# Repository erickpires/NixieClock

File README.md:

# The Project

This is a clock that uses Nixie Tubes as display. The idea is not new and there are hundreds of others Nixie based clock on the internet.
I got inspired to build the clock after watching a video from [Techmoan](https://www.youtube.com/channel/UC5I2hjZYiW9gZPVkvzM8_Cw).

## The Nixies

The Nixie Tubes were bought from eBay. They are IN-14 tubes desoldered from unused replacement board for old equipment (so the seller told me).

To drive the Nixies, six K155ID1 (the Russian version of the 74141) were also bought from eBay (which turned out to be a bad idea since those chips are very old, not reliable and consume too much power).

The Nixies are powered with 170V and half of their nominal amperage (this should extend their lifetime).

## The Boards

The clock is divided in three boards: a High-Voltage Power Supply for the Nixie Tubes, a Logic Board and a board to hold the Nixies.

* The Power Supply was built on a prototyping PCB based on two designs found online. More information can be found on the Power Supply directory of this repository.

* The Logic Board contains an Atmel Atmega 328p microcontroller which implements the clock in software. This board also contains some passive components and connectors. The schematic and the PCB design was done using kicad and can be found under the kicad/LowerBoard directory. The board itself was homemade using the toner transfer technique (more information can be found online) and etched using ferric chloride.

* The third board holds the Nixie Tubes as well as the six driver ICs and three 74HC573 8-bit transparent latches. This board also functions as the upper face of the clock and the ICs were put in this board because I thought it would be more aesthetically pleasing. The PCB design can be found under the kicad/Clock directory. This board was made using the same technique as the Logic Board.

## The Code

The code runs on an Atmega 328p with an Arduino bootloader. The code doesn't use any of the Arduino library functions, accessing registers directly. The code should work fine without the Arduino environment and using the Atmel Studio. The Arduino environment is used only to provide a n easy way of uploading the code into the microcontroller.

The clock is implemented in software, as already mentioned. The code also handles debouncing of the input buttons and rotary encoder.

Every whole minute the clock plays an animation in which all digits of all Nixie Tubes are lit twice. The primary reason for the animation is to avoid [Cathode Poisoning](http://www.tube-tester.com/sites/nixie/different/cathode%20poisoning/cathode-poisoning.htm) since must of the digits don't change too often (and some digits aren't even lit) but also because it looks cool.

From midnight to 6AM the display is shutdown. This should save some lifetime out of the Nixies. Upon interaction with any button (or rotary encoder) while the display is off, it turns on for 5 seconds.

An alarm clock functionality is planned, but not yet implemented.

## Final Result

Here are two photos of the clock working.

and a video:

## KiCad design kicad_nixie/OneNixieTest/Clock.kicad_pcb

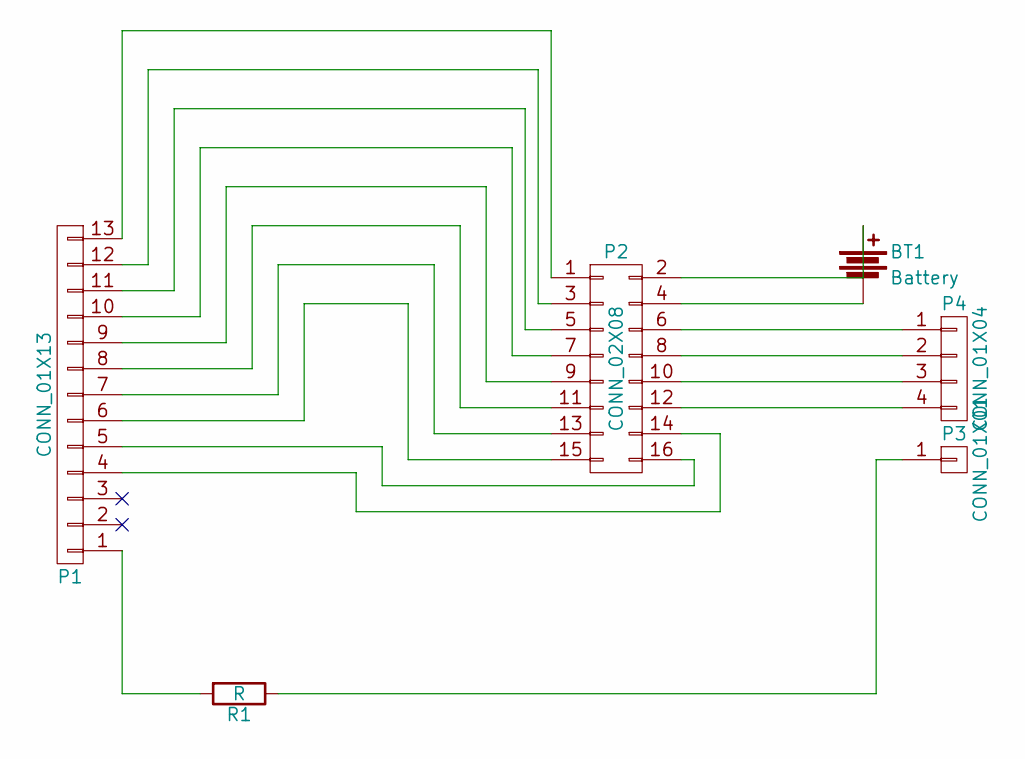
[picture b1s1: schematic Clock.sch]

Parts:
BT1: Battery; Pin_Header_Straight_1x02
P1: CONN_01X13; IN-14-mod
P2: CONN_02X08; DIP-16_W7.62mm_LongPads
P3: CONN_01X01; Pin_Header_Straight_1x01
P4: CONN_01X04; Pin_Header_Straight_1x04
R1: R; Resistor_Horizontal_RM10mm

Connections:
unnamed: BT1.1, P2.2
unnamed: BT1.2, P2.4
unnamed: P1.1, R1.2
unnamed: P1.4, P2.14
unnamed: P1.5, P2.16
unnamed: P1.6, P2.15
unnamed: P1.7, P2.13
unnamed: P1.8, P2.11
unnamed: P1.9, P2.9
unnamed: P1.10, P2.7
unnamed: P1.11, P2.5
unnamed: P1.12, P2.3
unnamed: P1.13, P2.1
unnamed: P2.6, P4.1
unnamed: P2.8, P4.2
unnamed: P2.10, P4.3
unnamed: P2.12, P4.4
unnamed: P3.1, R1.1

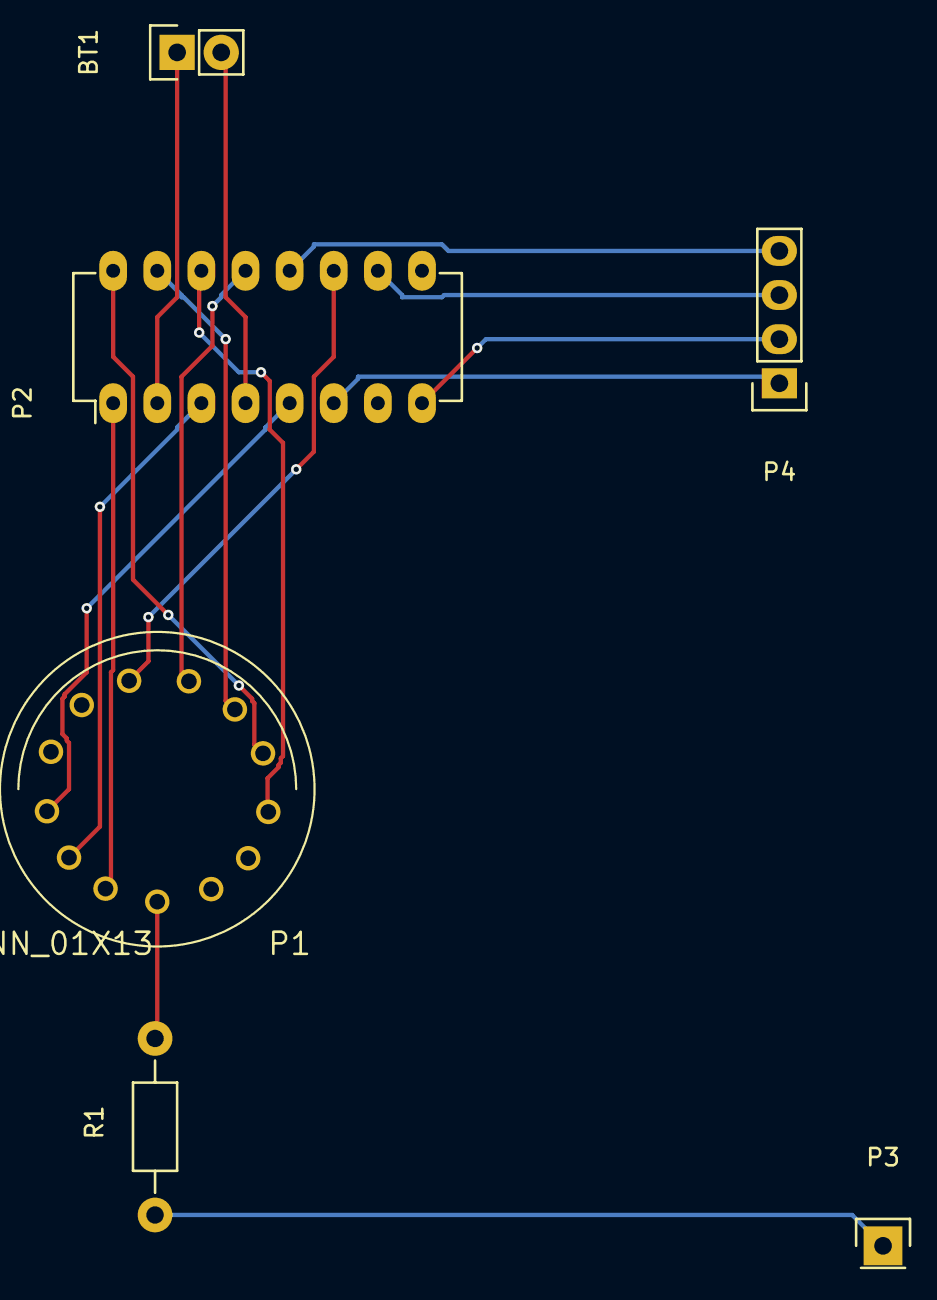
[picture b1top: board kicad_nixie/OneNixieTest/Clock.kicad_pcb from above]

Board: 2 copper layers, 6 parts (0 on the bottom side), 18 nets.

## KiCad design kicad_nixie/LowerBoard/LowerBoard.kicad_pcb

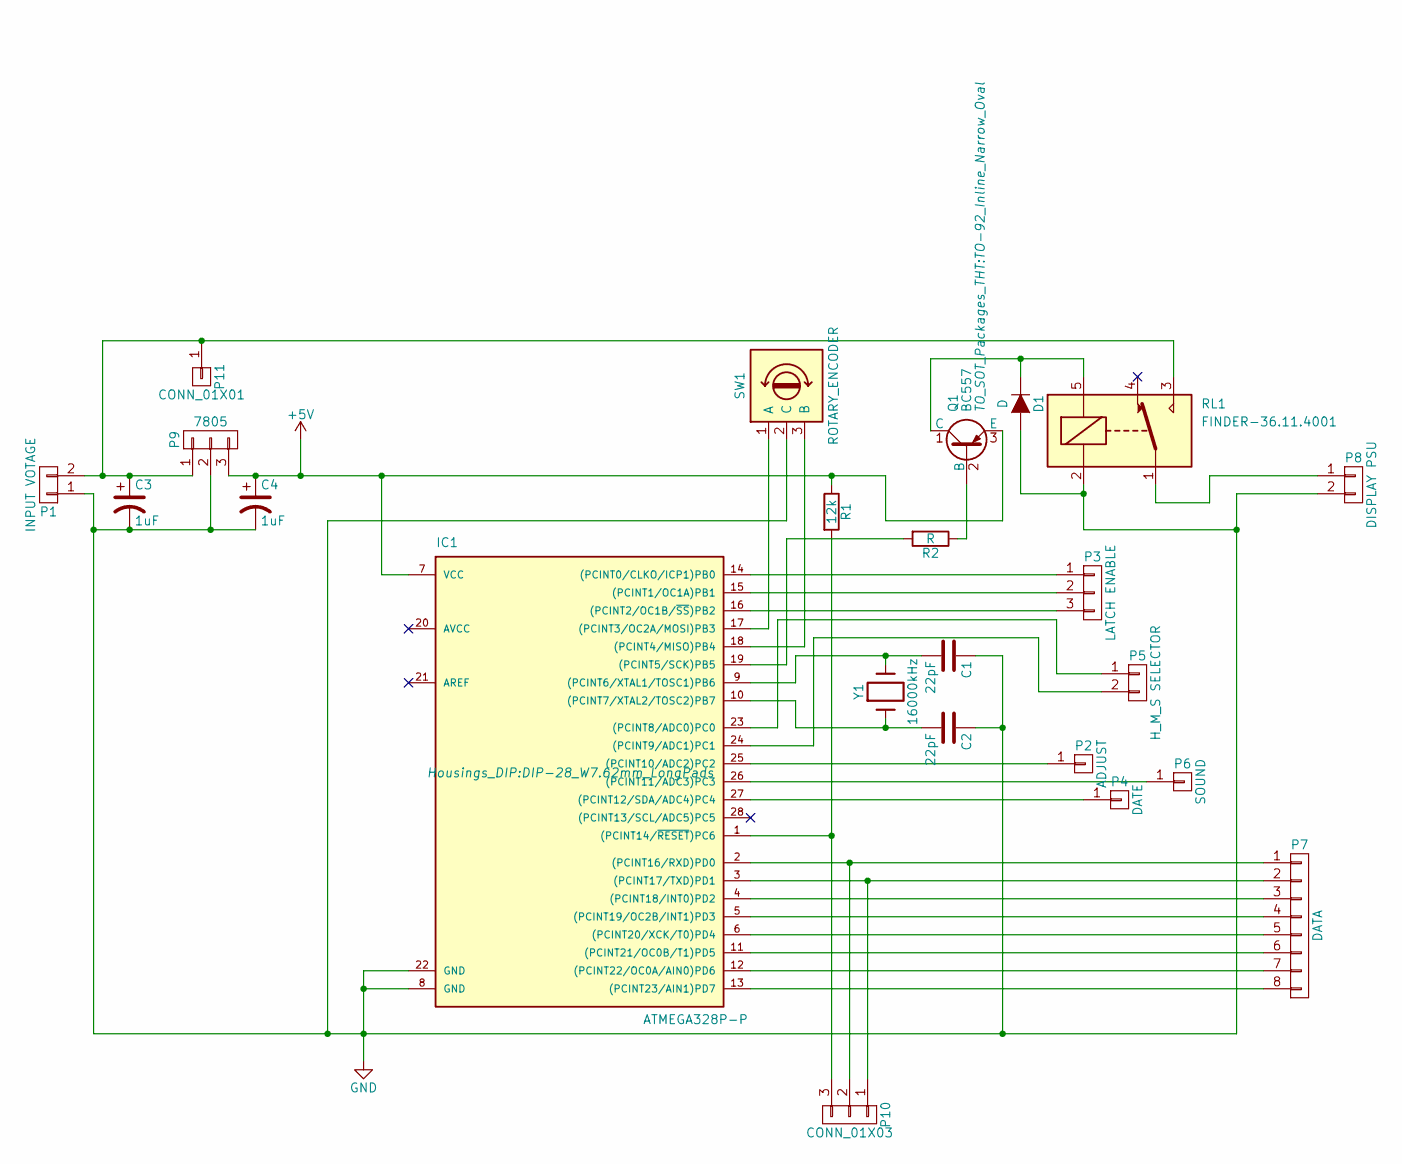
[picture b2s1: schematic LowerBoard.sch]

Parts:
C1, C2: 22pF; C_Disc_D3_P2.5
C3, C4: 1uF; C_Radial_D5_L11_P2.5
D1: D; Diode_DO-35_SOD27_Horizontal_RM10
IC1: ATMEGA328P-P; DIP-28_W7.62mm_LongPads
P1: INPUT VOTAGE; Pin_Header_Straight_1x02
P2: ADJUST; Pin_Header_Straight_1x01
P3: LATCH ENABLE; Pin_Header_Straight_1x03
P4: DATE; Pin_Header_Straight_1x01
P5: H_M_S SELECTOR; Pin_Header_Straight_1x02
P6: SOUND; Pin_Header_Straight_1x01
P7: DATA; Pin_Header_Straight_1x08
P8: DISPLAY PSU; Pin_Header_Straight_1x02
P9: 7805; TO-220
P10: CONN_01X03; Pin_Header_Straight_1x03
P11: CONN_01X01; Pin_Header_Straight_1x01
Q1: BC557; TO-92_Inline_Narrow_Oval
R1: 12k; Resistor_Horizontal_RM7mm
R2: R; Resistor_Horizontal_RM7mm
RL1: FINDER-36.11.4001; Relay_SANYOU_SRD_Series_Form_C
SW1: ROTARY_ENCODER; Pin_Header_Straight_1x03
Y1: 16000kHz; Crystal_HC50-U_Vertical

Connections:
+5V: C4.1, IC1.7 (VCC), P9.3, Q1.3 (E), R1.1
GND: C1.1, C2.1, C3.2, C4.2, D1.2 (A), IC1.8 (GND), IC1.22 (GND), P1.1, P8.2, P9.2, RL1.2, SW1.2 (C)
unnamed: C1.2, IC1.9 ((PCINT6/XTAL1/TOSC1)PB6), Y1.2
unnamed: C2.2, IC1.10 ((PCINT7/XTAL2/TOSC2)PB7), Y1.1
unnamed: C3.1, P1.2, P9.1, P11.1, RL1.3
unnamed: D1.1 (K), Q1.1 (C), RL1.5
unnamed: IC1.1 ((PCINT14/~RESET~)PC6), P10.3, R1.2
unnamed: IC1.2 ((PCINT16/RXD)PD0), P7.1, P10.2
unnamed: IC1.3 ((PCINT17/TXD)PD1), P7.2, P10.1
unnamed: IC1.4 ((PCINT18/INT0)PD2), P7.3
unnamed: IC1.5 ((PCINT19/OC2B/INT1)PD3), P7.4
unnamed: IC1.6 ((PCINT20/XCK/T0)PD4), P7.5
unnamed: IC1.11 ((PCINT21/OC0B/T1)PD5), P7.6
unnamed: IC1.12 ((PCINT22/OC0A/AIN0)PD6), P7.7
unnamed: IC1.13 ((PCINT23/AIN1)PD7), P7.8
unnamed: IC1.14 ((PCINT0/CLKO/ICP1)PB0), P3.1
unnamed: IC1.15 ((PCINT1/OC1A)PB1), P3.2
unnamed: IC1.16 ((PCINT2/OC1B/~SS~)PB2), P3.3
unnamed: IC1.17 ((PCINT3/OC2A/MOSI)PB3), SW1.1 (A)
unnamed: IC1.18 ((PCINT4/MISO)PB4), SW1.3 (B)
unnamed: IC1.19 ((PCINT5/SCK)PB5), R2.2
unnamed: IC1.23 ((PCINT8/ADC0)PC0), P5.1
unnamed: IC1.24 ((PCINT9/ADC1)PC1), P5.2
unnamed: IC1.25 ((PCINT10/ADC2)PC2), P2.1
unnamed: IC1.26 ((PCINT11/ADC3)PC3), P6.1
unnamed: IC1.27 ((PCINT12/SDA/ADC4)PC4), P4.1
unnamed: P8.1, RL1.1
unnamed: Q1.2 (B), R2.1

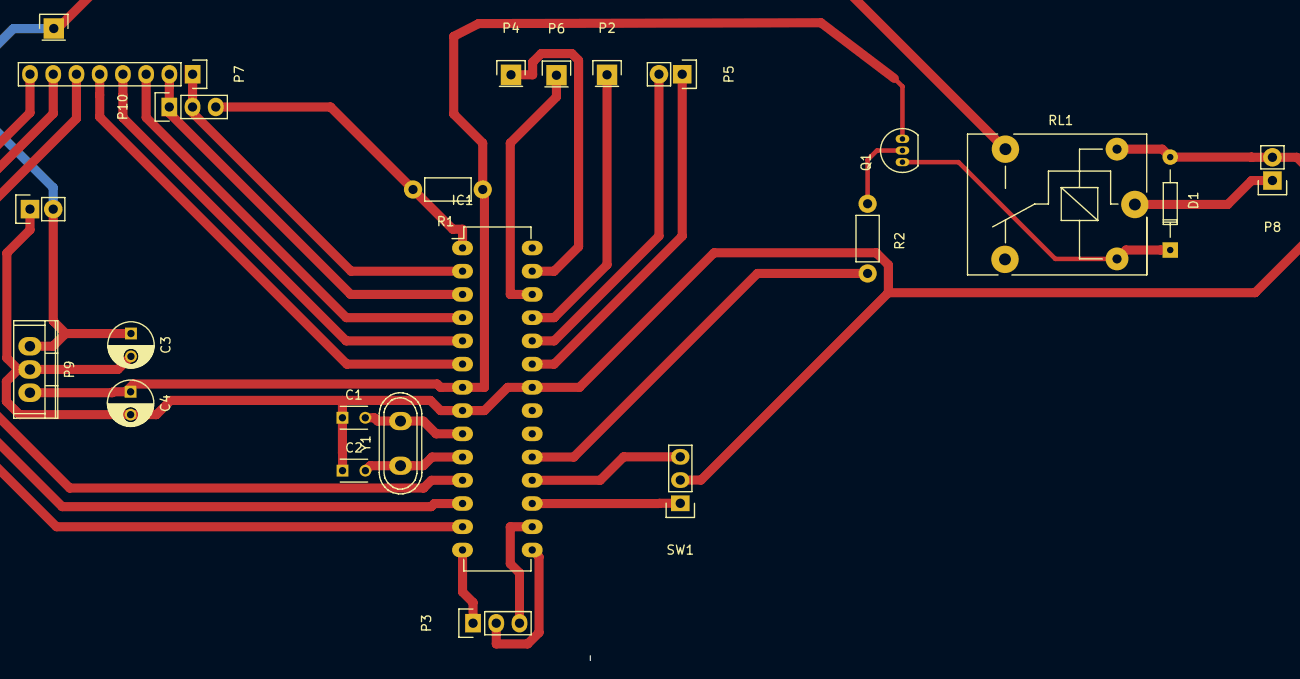
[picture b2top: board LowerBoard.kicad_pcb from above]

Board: 2 copper layers, 23 parts (0 on the bottom side), 28 nets.

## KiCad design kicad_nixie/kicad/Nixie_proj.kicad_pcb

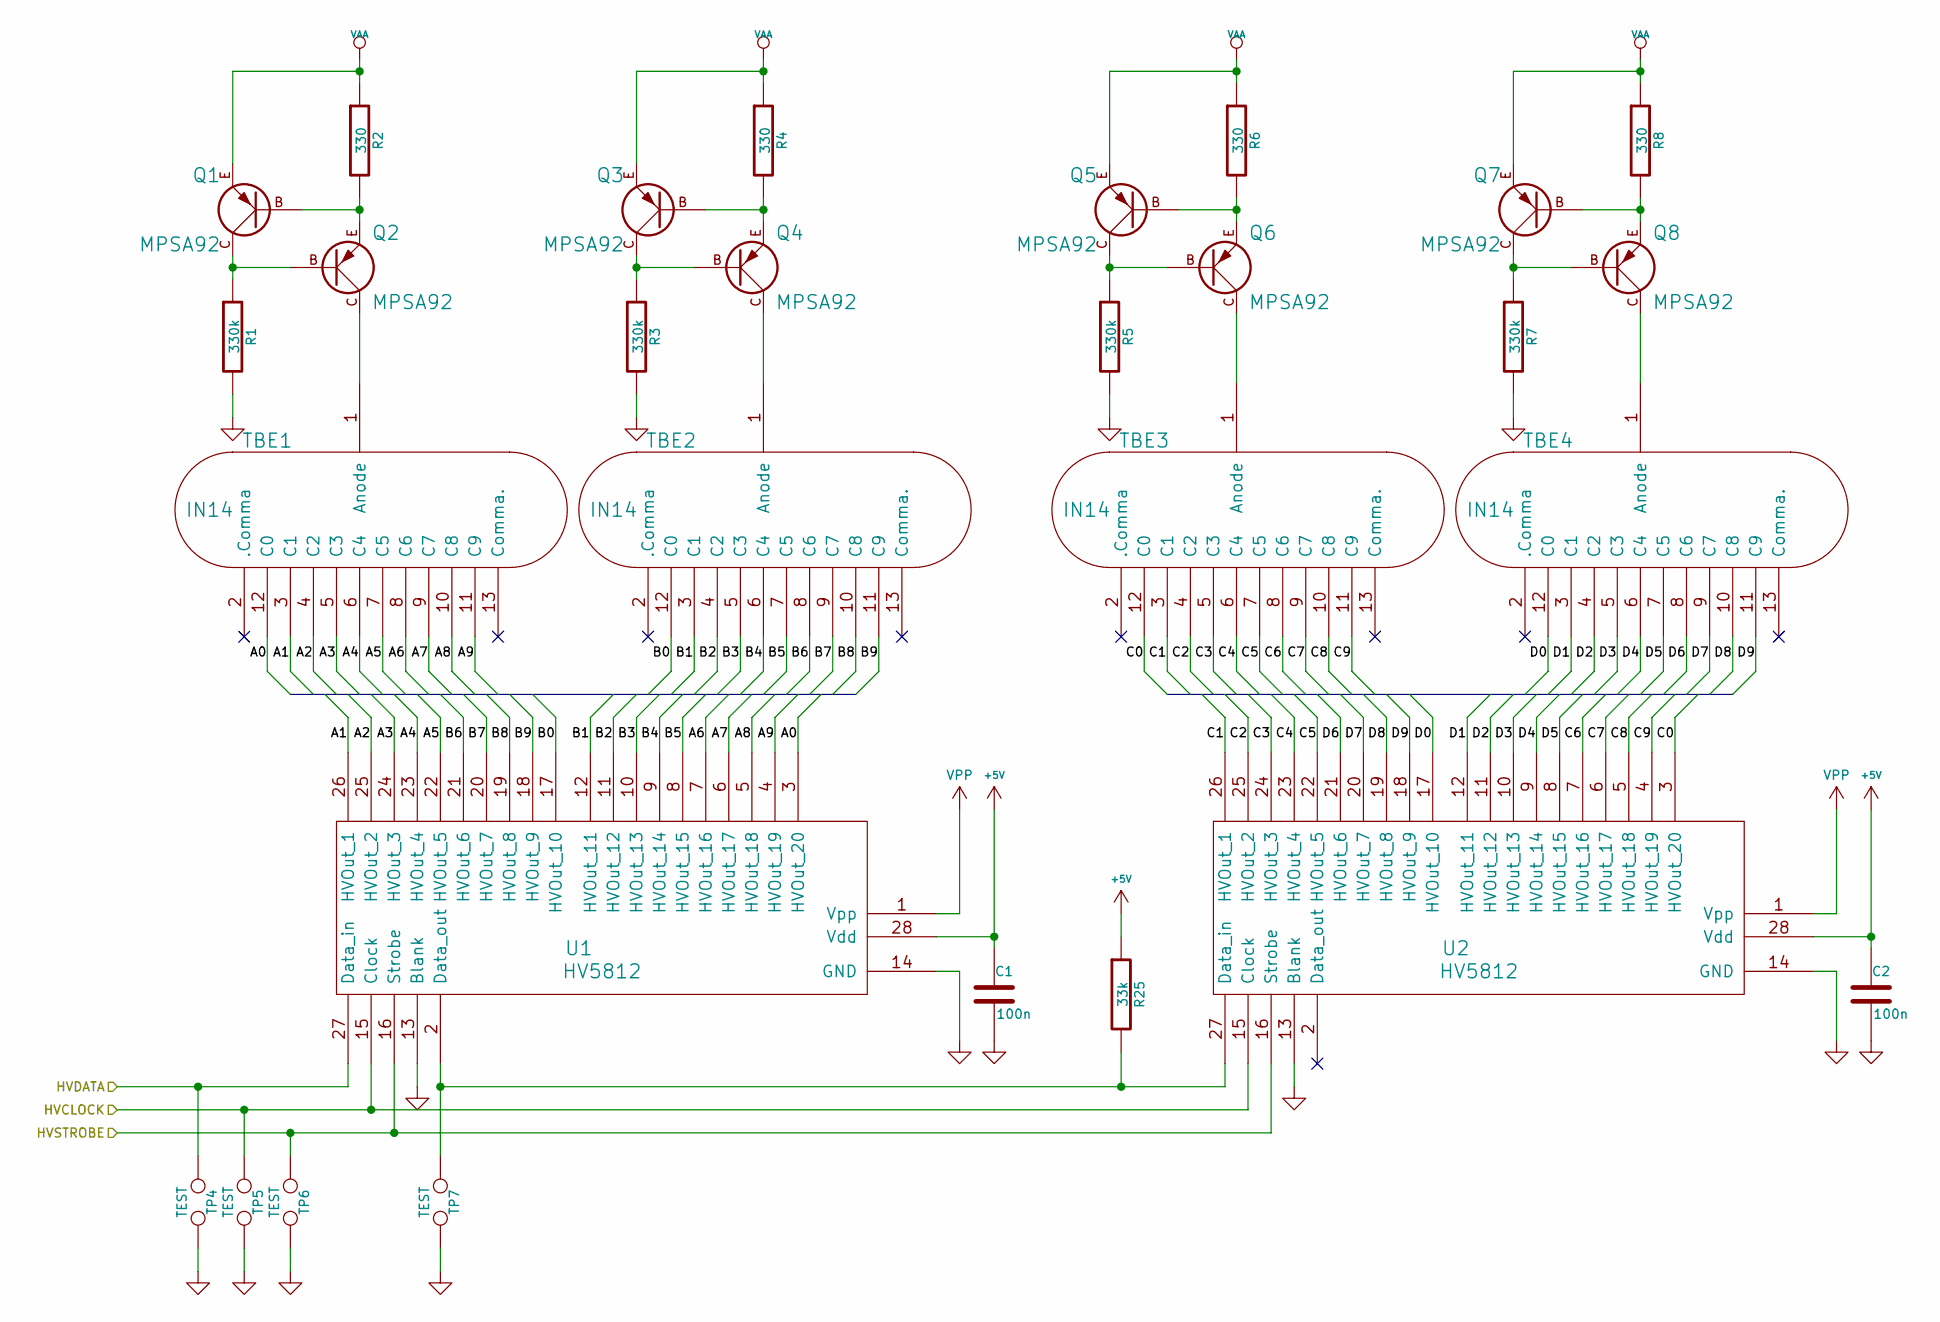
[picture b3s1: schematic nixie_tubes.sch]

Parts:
C1, C2: 100n; c_0805
Q1, Q2, Q3, Q4, Q5, Q6, Q7, Q8: MPSA92; TO92-CBE
R1, R3, R5, R7: 330k; R3-mod
R2, R4, R6, R8: 330; R3-mod
R25: 33k; R0805_smd-mod
TBE1, TBE2, TBE3, TBE4: IN14; IN-14-mod
TP4, TP5, TP6, TP7: TEST; GS2
U1, U2: HV5812; SO28W-mod

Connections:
+5V: C1.1, C2.1, R25.1, U1.28 (Vdd), U2.28 (Vdd); also elsewhere on the board
/Microcontroller and clock/HVCLOCK: TP5.1, U1.15 (Clock), U2.15 (Clock); also elsewhere on the board
/Microcontroller and clock/HVDATA: TP4.1, U1.27 (Data_in); also elsewhere on the board
/Microcontroller and clock/HVSTROBE: TP6.1, U1.16 (Strobe), U2.16 (Strobe); also elsewhere on the board
/Tubes with drivers/A0: TBE1.12 (C0), U1.3 (HVOut_20)
/Tubes with drivers/A1: TBE1.3 (C1), U1.26 (HVOut_1)
/Tubes with drivers/A2: TBE1.4 (C2), U1.25 (HVOut_2)
/Tubes with drivers/A3: TBE1.5 (C3), U1.24 (HVOut_3)
/Tubes with drivers/A4: TBE1.6 (C4), U1.23 (HVOut_4)
/Tubes with drivers/A5: TBE1.7 (C5), U1.22 (HVOut_5)
/Tubes with drivers/A6: TBE1.8 (C6), U1.7 (HVOut_16)
/Tubes with drivers/A7: TBE1.9 (C7), U1.6 (HVOut_17)
/Tubes with drivers/A8: TBE1.10 (C8), U1.5 (HVOut_18)
/Tubes with drivers/A9: TBE1.11 (C9), U1.4 (HVOut_19)
/Tubes with drivers/B0: TBE2.12 (C0), U1.17 (HVOut_10)
/Tubes with drivers/B1: TBE2.3 (C1), U1.12 (HVOut_11)
/Tubes with drivers/B2: TBE2.4 (C2), U1.11 (HVOut_12)
/Tubes with drivers/B3: TBE2.5 (C3), U1.10 (HVOut_13)
/Tubes with drivers/B4: TBE2.6 (C4), U1.9 (HVOut_14)
/Tubes with drivers/B5: TBE2.7 (C5), U1.8 (HVOut_15)
/Tubes with drivers/B6: TBE2.8 (C6), U1.21 (HVOut_6)
/Tubes with drivers/B7: TBE2.9 (C7), U1.20 (HVOut_7)
/Tubes with drivers/B8: TBE2.10 (C8), U1.19 (HVOut_8)
/Tubes with drivers/B9: TBE2.11 (C9), U1.18 (HVOut_9)
/Tubes with drivers/C0: TBE3.12 (C0), U2.3 (HVOut_20)
/Tubes with drivers/C1: TBE3.3 (C1), U2.26 (HVOut_1)
/Tubes with drivers/C2: TBE3.4 (C2), U2.25 (HVOut_2)
/Tubes with drivers/C3: TBE3.5 (C3), U2.24 (HVOut_3)
/Tubes with drivers/C4: TBE3.6 (C4), U2.23 (HVOut_4)
/Tubes with drivers/C5: TBE3.7 (C5), U2.22 (HVOut_5)
/Tubes with drivers/C6: TBE3.8 (C6), U2.7 (HVOut_16)
/Tubes with drivers/C7: TBE3.9 (C7), U2.6 (HVOut_17)
/Tubes with drivers/C8: TBE3.10 (C8), U2.5 (HVOut_18)
/Tubes with drivers/C9: TBE3.11 (C9), U2.4 (HVOut_19)
/Tubes with drivers/D0: TBE4.12 (C0), U2.17 (HVOut_10)
/Tubes with drivers/D1: TBE4.3 (C1), U2.12 (HVOut_11)
/Tubes with drivers/D2: TBE4.4 (C2), U2.11 (HVOut_12)
/Tubes with drivers/D3: TBE4.5 (C3), U2.10 (HVOut_13)
/Tubes with drivers/D4: TBE4.6 (C4), U2.9 (HVOut_14)
/Tubes with drivers/D5: TBE4.7 (C5), U2.8 (HVOut_15)
/Tubes with drivers/D6: TBE4.8 (C6), U2.21 (HVOut_6)
/Tubes with drivers/D7: TBE4.9 (C7), U2.20 (HVOut_7)
/Tubes with drivers/D8: TBE4.10 (C8), U2.19 (HVOut_8)
/Tubes with drivers/D9: TBE4.11 (C9), U2.18 (HVOut_9)
GND: C1.2, C2.2, R1.2, R3.2, R5.2, R7.2, TP4.2, TP5.2, TP6.2, TP7.2, U1.13 (Blank), U1.14 (GND), U2.13 (Blank), U2.14 (GND); also elsewhere on the board
unnamed: Q1.B, Q2.E, R2.2
unnamed: Q1.C, Q2.B, R1.1
unnamed: Q2.C, TBE1.1 (Anode)
unnamed: Q3.B, Q4.E, R4.2
unnamed: Q3.C, Q4.B, R3.1
unnamed: Q4.C, TBE2.1 (Anode)
unnamed: Q5.B, Q6.E, R6.2
unnamed: Q5.C, Q6.B, R5.1
unnamed: Q6.C, TBE3.1 (Anode)
unnamed: Q7.B, Q8.E, R8.2
unnamed: Q7.C, Q8.B, R7.1
unnamed: Q8.C, TBE4.1 (Anode)
unnamed: R25.2, TP7.1, U1.2 (Data_out), U2.27 (Data_in)
VAA: Q1.E, Q3.E, Q5.E, Q7.E, R2.1, R4.1, R6.1, R8.1; also elsewhere on the board
VPP: U1.1 (Vpp), U2.1 (Vpp); also elsewhere on the board

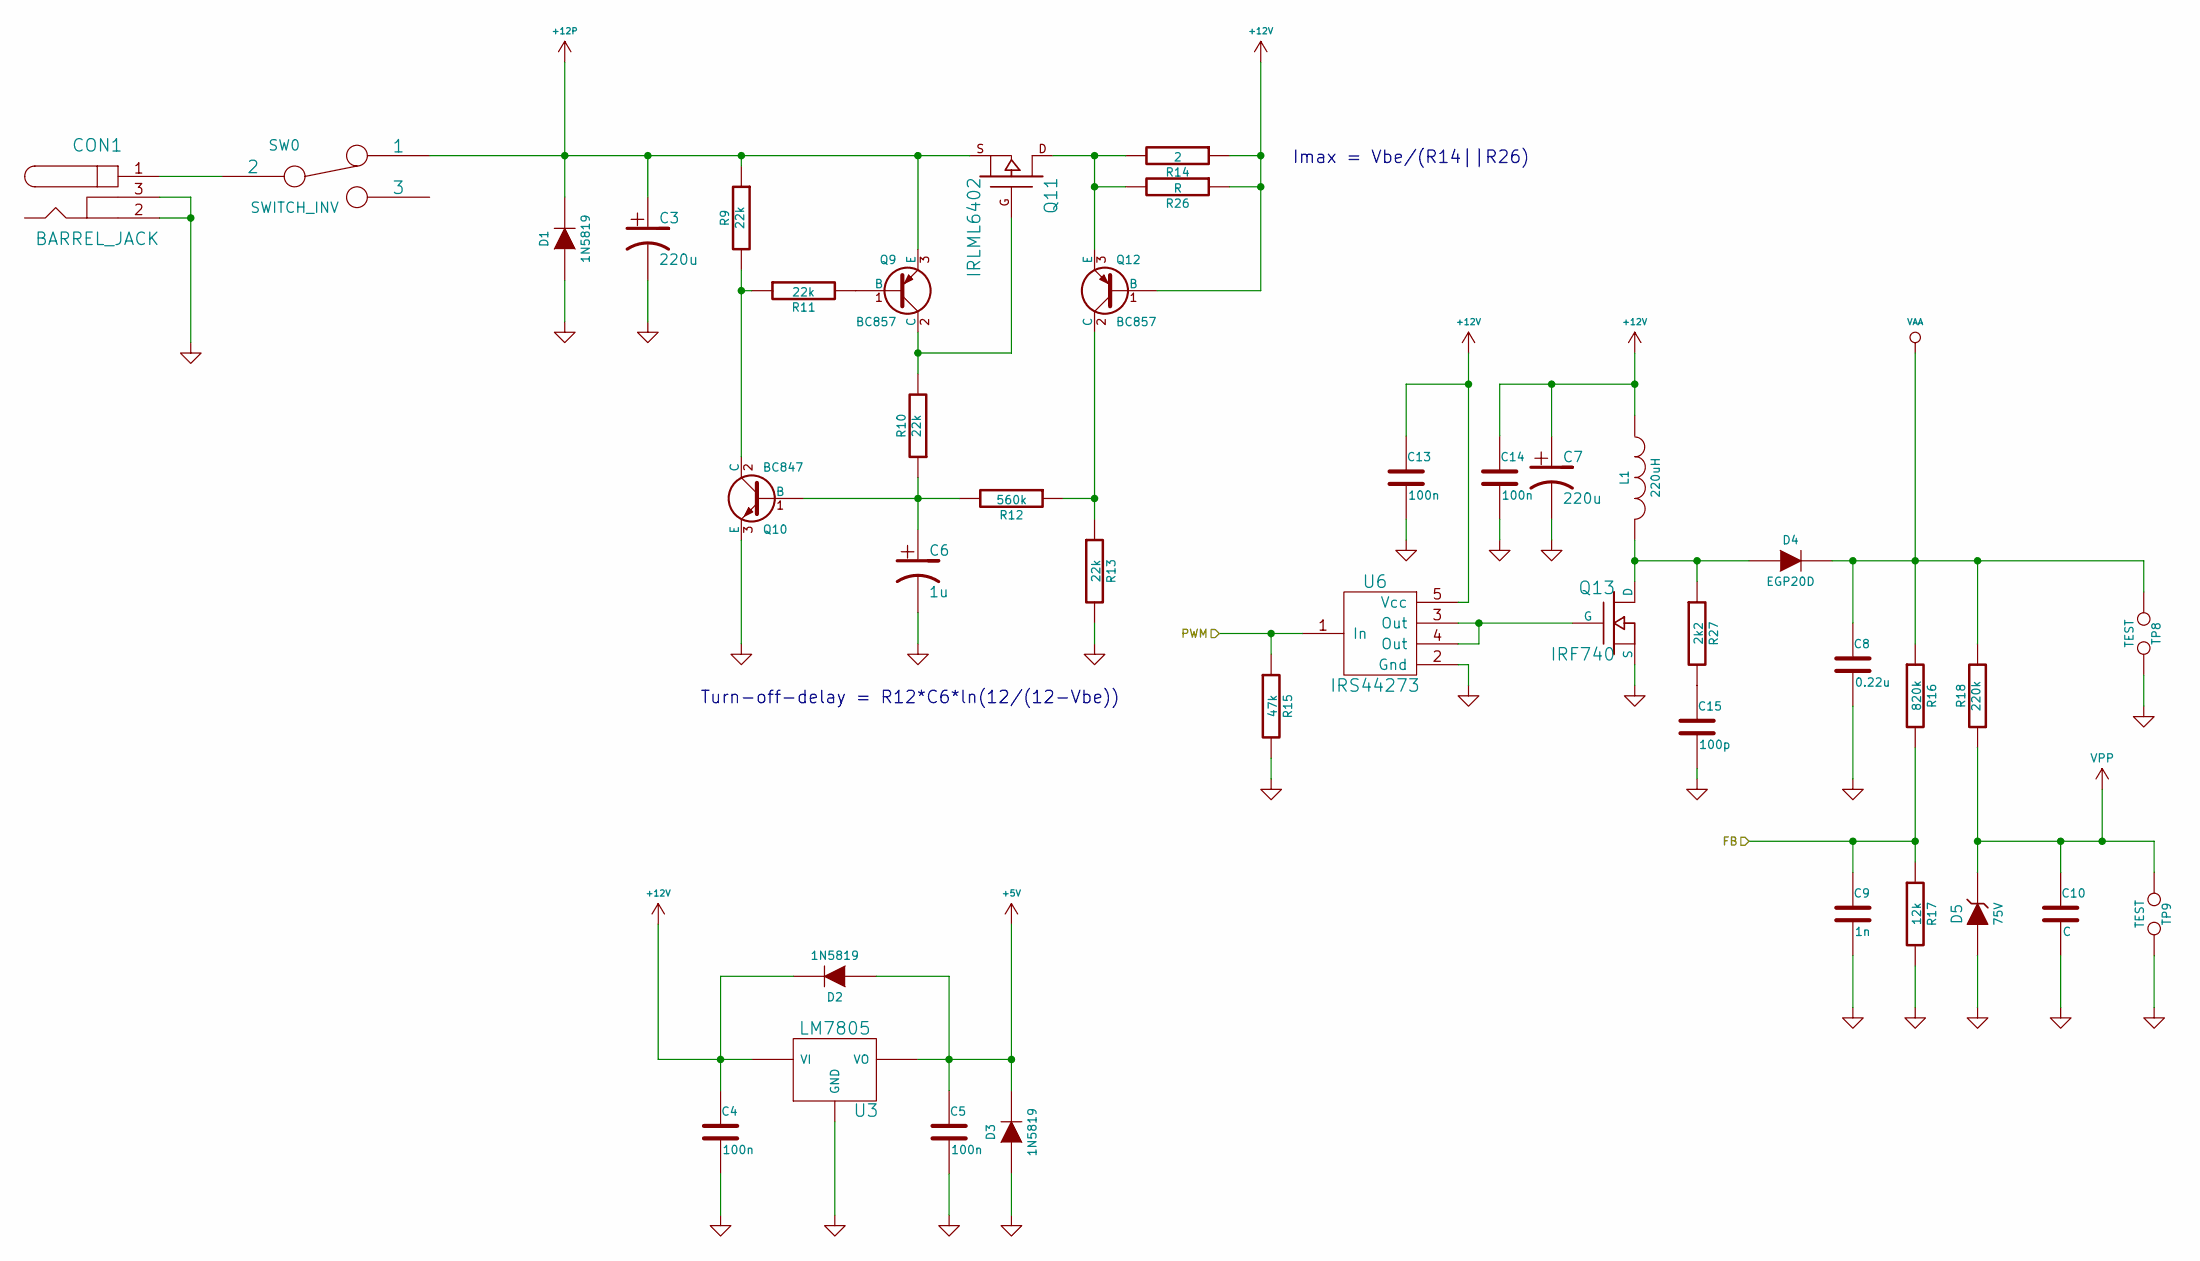
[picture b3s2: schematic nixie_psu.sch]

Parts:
C3, C7: 220u; CP_8x13mm
C4, C5, C13, C14: 100n; c_0805
C6: 1u; CP_5x6mm
C8: 0.22u; C102-054X133
C9: 1n; c_0805
C10: C; c_0805
C15: 100p; c_0805
CON1: BARREL_JACK
D1, D2, D3: 1N5819; D3
D4: EGP20D; D3
D5: 75V; D3
L1: 220uH; INDUCTOR_V
Q9, Q12: BC857; sot23
Q10: BC847; sot23
Q11: IRLML6402; SOT23GDS
Q13: IRF740; TO220GDS_VERT
R9, R10, R11, R13: 22k; R0805_smd-mod
R12: 560k; R0805_smd-mod
R14: 2; R3-mod
R15: 47k; R0805_smd-mod
R16: 820k; R3-mod
R17: 12k; R3-mod
R18: 220k; R3-mod
R26: R; R3-mod
R27: 2k2; R3-mod
SW0: SWITCH_INV; CL-SA-12C4-02
TP8, TP9: TEST; GS2
U3: LM7805; TO-220
U6: IRS44273; SOT23-5

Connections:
+5V: C5.1, D2.1 (A), D3.2 (K), U3.3 (VO); also elsewhere on the board
+12P: C3.1, D1.2 (K), Q9.3 (E), Q11.S, R9.1, SW0.1
+12V: C4.1, C7.1, C13.1, C14.1, D2.2 (K), L1.1, Q12.1 (B), R14.1, R26.1, U3.1 (VI), U6.5 (Vcc)
/Microcontroller and clock/FB: C9.1, R16.2, R17.1; also elsewhere on the board
/Microcontroller and clock/PWM: R15.1, U6.1 (In); also elsewhere on the board
GND: C3.2, C4.2, C5.2, C6.2, C7.2, C8.2, C9.2, C10.2, C13.2, C14.2, C15.2, CON1.2, CON1.3, D1.1 (A), D3.1 (A), D5.1 (A), Q10.3 (E), Q13.S, R13.2, R15.2, R17.2, TP8.2, TP9.2, U3.2 (GND), U6.2 (Gnd); also elsewhere on the board
unnamed: C6.1, Q10.1 (B), R10.1, R12.2
unnamed: C15.1, R27.2
unnamed: CON1.1, SW0.2
unnamed: D4.1 (A), L1.2, Q13.D, R27.1
unnamed: Q9.1 (B), R11.2
unnamed: Q10.2 (C), R9.2, R11.1
unnamed: Q11.D, Q12.3 (E), R14.2, R26.2
unnamed: Q9.2 (C), Q11.G, R10.2
unnamed: Q12.2 (C), R12.1, R13.1
unnamed: Q13.G, U6.3 (Out), U6.4 (Out)
VAA: C8.1, D4.2 (K), R16.1, R18.2, TP8.1; also elsewhere on the board
VPP: C10.1, D5.2 (K), R18.1, TP9.1; also elsewhere on the board

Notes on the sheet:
Imax = Vbe/(R14||R26)
Turn-off-delay = R12*C6*ln(12/(12-Vbe))

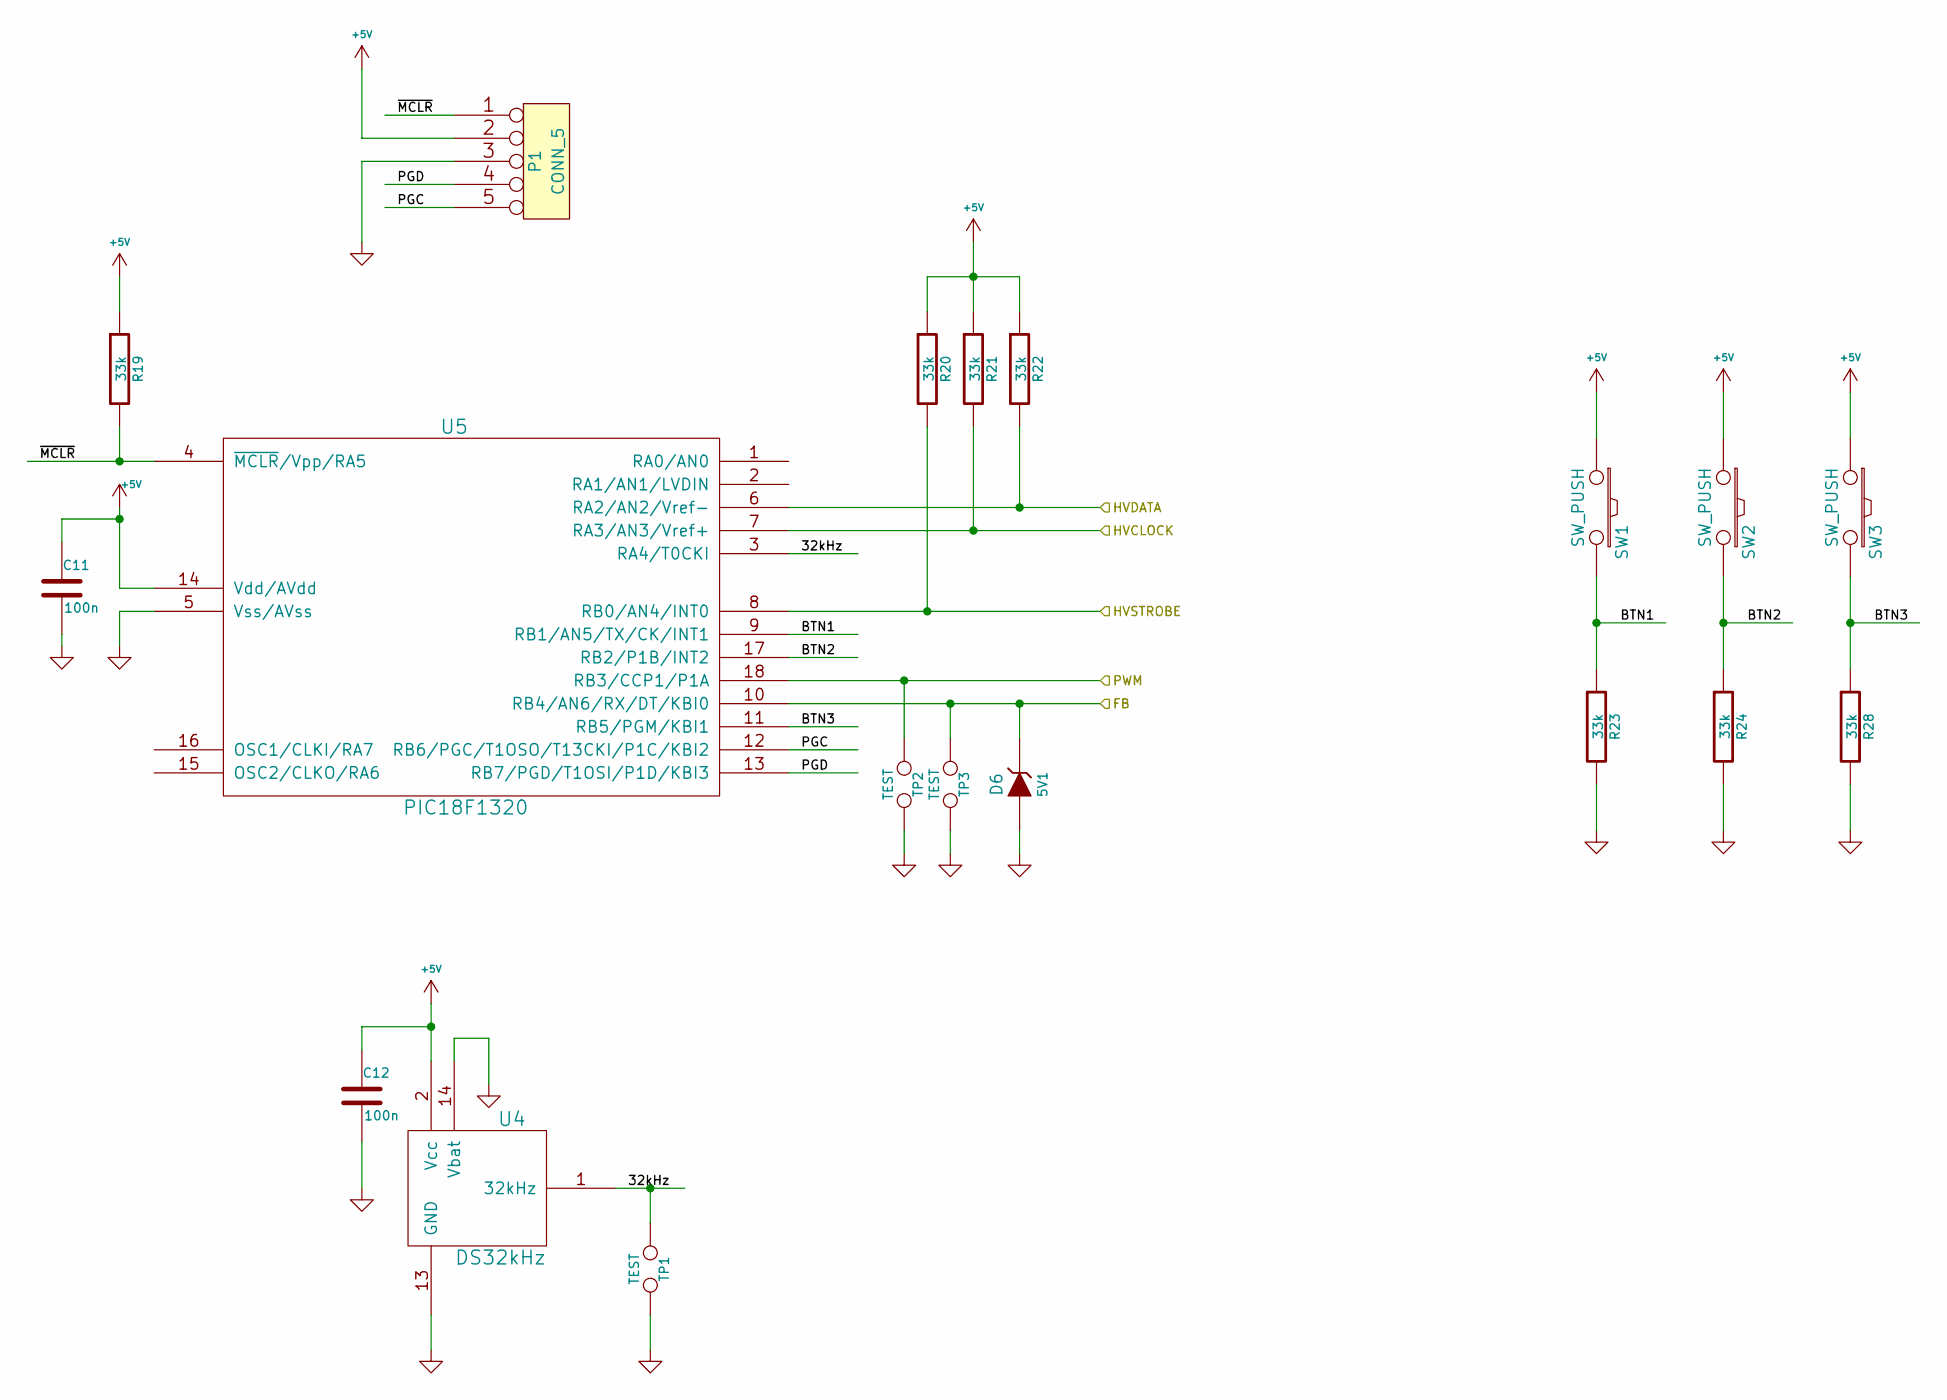
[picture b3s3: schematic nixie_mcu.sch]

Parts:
C11, C12: 100n; c_0805
D6: 5V1; D3
P1: CONN_5; PIN_ARRAY_5x1
R19, R20, R21, R22, R23, R24, R28: 33k; R0805_smd-mod
SW1, SW2, SW3: SW_PUSH; TL1105L-4,3
TP1, TP2, TP3: TEST; GS2
U4: DS32kHz; SO16W-mod
U5: PIC18F1320; SO18L-mod

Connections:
+5V: C11.1, C12.1, P1.2, R19.1, R20.1, R21.1, R22.1, SW1.1, SW2.1, SW3.1, U4.2 (Vcc), U5.14 (Vdd/AVdd); also elsewhere on the board
/Microcontroller and clock/32kHz: TP1.1, U4.1 (32kHz), U5.3 (RA4/T0CKI)
/Microcontroller and clock/BTN1: R23.1, SW1.2, U5.9 (RB1/AN5/TX/CK/INT1)
/Microcontroller and clock/BTN2: R24.1, SW2.2, U5.17 (RB2/P1B/INT2)
/Microcontroller and clock/BTN3: R28.1, SW3.2, U5.11 (RB5/PGM/KBI1)
/Microcontroller and clock/FB: D6.2 (K), TP3.1, U5.10 (RB4/AN6/RX/DT/KBI0); also elsewhere on the board
/Microcontroller and clock/HVCLOCK: R21.2, U5.7 (RA3/AN3/Vref+); also elsewhere on the board
/Microcontroller and clock/HVDATA: R22.2, U5.6 (RA2/AN2/Vref-); also elsewhere on the board
/Microcontroller and clock/HVSTROBE: R20.2, U5.8 (RB0/AN4/INT0); also elsewhere on the board
/Microcontroller and clock/PGC: P1.5, U5.12 (RB6/PGC/T1OSO/T13CKI/P1C/KBI2)
/Microcontroller and clock/PGD: P1.4, U5.13 (RB7/PGD/T1OSI/P1D/KBI3)
/Microcontroller and clock/PWM: TP2.1, U5.18 (RB3/CCP1/P1A); also elsewhere on the board
/Microcontroller and clock/~MCLR: P1.1, R19.2, U5.4 (~MCLR~/Vpp/RA5)
GND: C11.2, C12.2, D6.1 (A), P1.3, R23.2, R24.2, R28.2, TP1.2, TP2.2, TP3.2, U4.13 (GND), U4.14 (Vbat), U5.5 (Vss/AVss); also elsewhere on the board

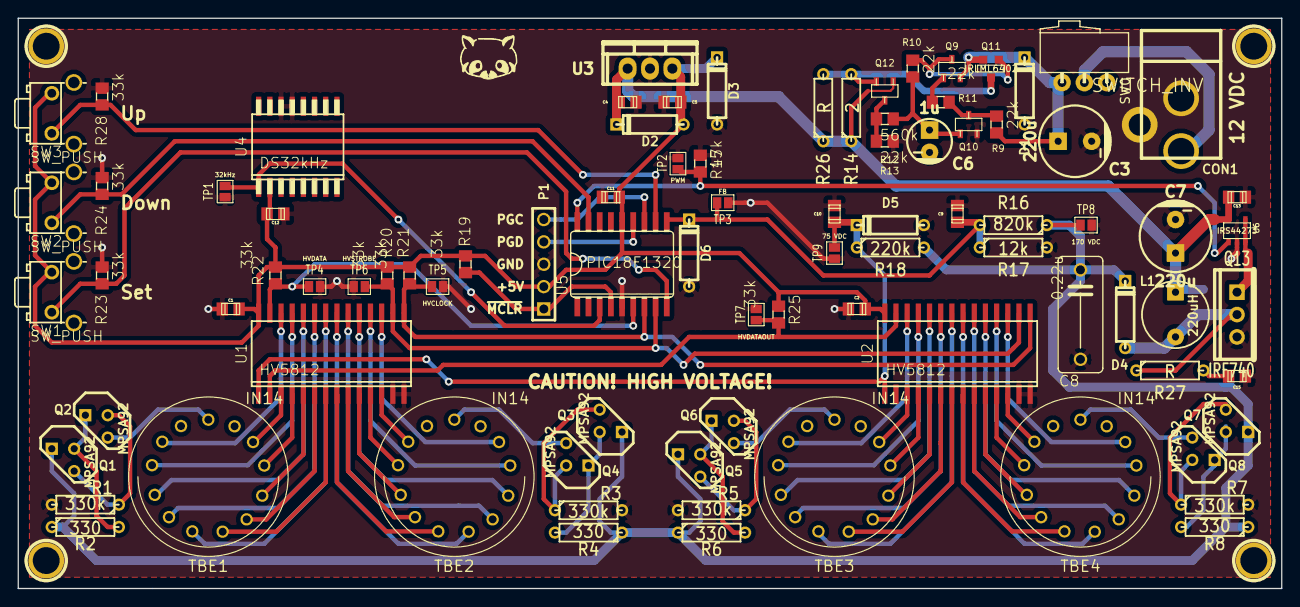
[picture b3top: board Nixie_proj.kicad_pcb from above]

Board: 2 copper layers, 143.5 x 64.8 mm, 93 parts (1 on the bottom side), 81 nets.

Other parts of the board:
1PIN, 1PIN#2, 1PIN#3, 1PIN#4: P***; 1pin
Logo_ref: LOGO; Panda_Logo_7x5mm

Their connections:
GND: 1PIN.1, 1PIN#2.1, 1PIN#3.1, 1PIN#4.1; also elsewhere on the board
